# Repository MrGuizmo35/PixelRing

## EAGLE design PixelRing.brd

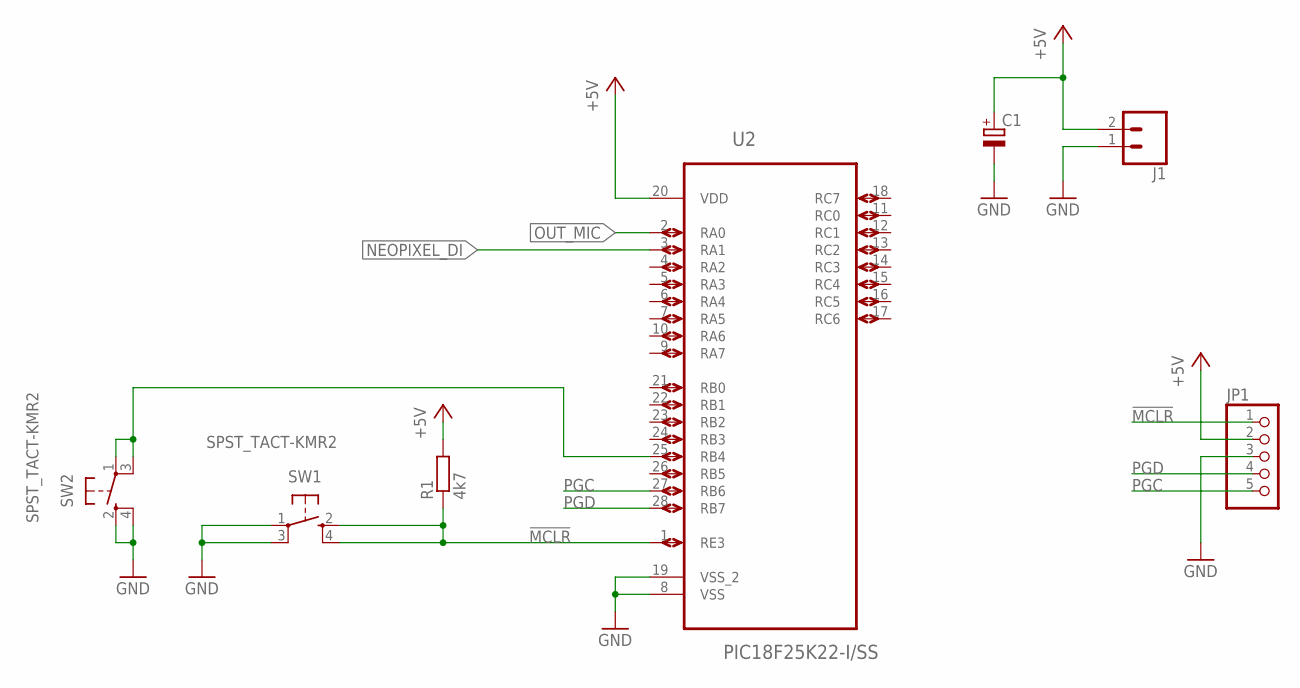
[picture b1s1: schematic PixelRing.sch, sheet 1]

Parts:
C1: CPOL-EUSMCB; SMC_B
J1: CONN_02-JST-2MM-SMT; JST-2-SMD
JP1: PINHD-1X5; 1X05
R1: 4k7; R0603
SW1, SW2: SPST_TACT-KMR2; KMR2
U2: PIC18F25K22-I/SS; SOP65P780X200-28N

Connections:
!MCLR: JP1.1, R1.1, SW1.2 (S), SW1.4 (S1), U2.1 (RE3)
+5V: C1.+, J1.2 (1), JP1.2, R1.2, U2.20 (VDD); also elsewhere on the board
GND: C1.-, J1.1 (2), JP1.3, SW1.1, SW1.3 (P1), SW2.2 (S), SW2.4 (S1), U2.8 (VSS), U2.19 (VSS_2); also elsewhere on the board
unnamed: SW2.1, SW2.3 (P1), U2.25 (RB4)
NEOPIXEL_DI: U2.3 (RA1); also elsewhere on the board
OUT_MIC: U2.2 (RA0); also elsewhere on the board
PGC: JP1.5, U2.27 (RB6)
PGD: JP1.4, U2.28 (RB7)

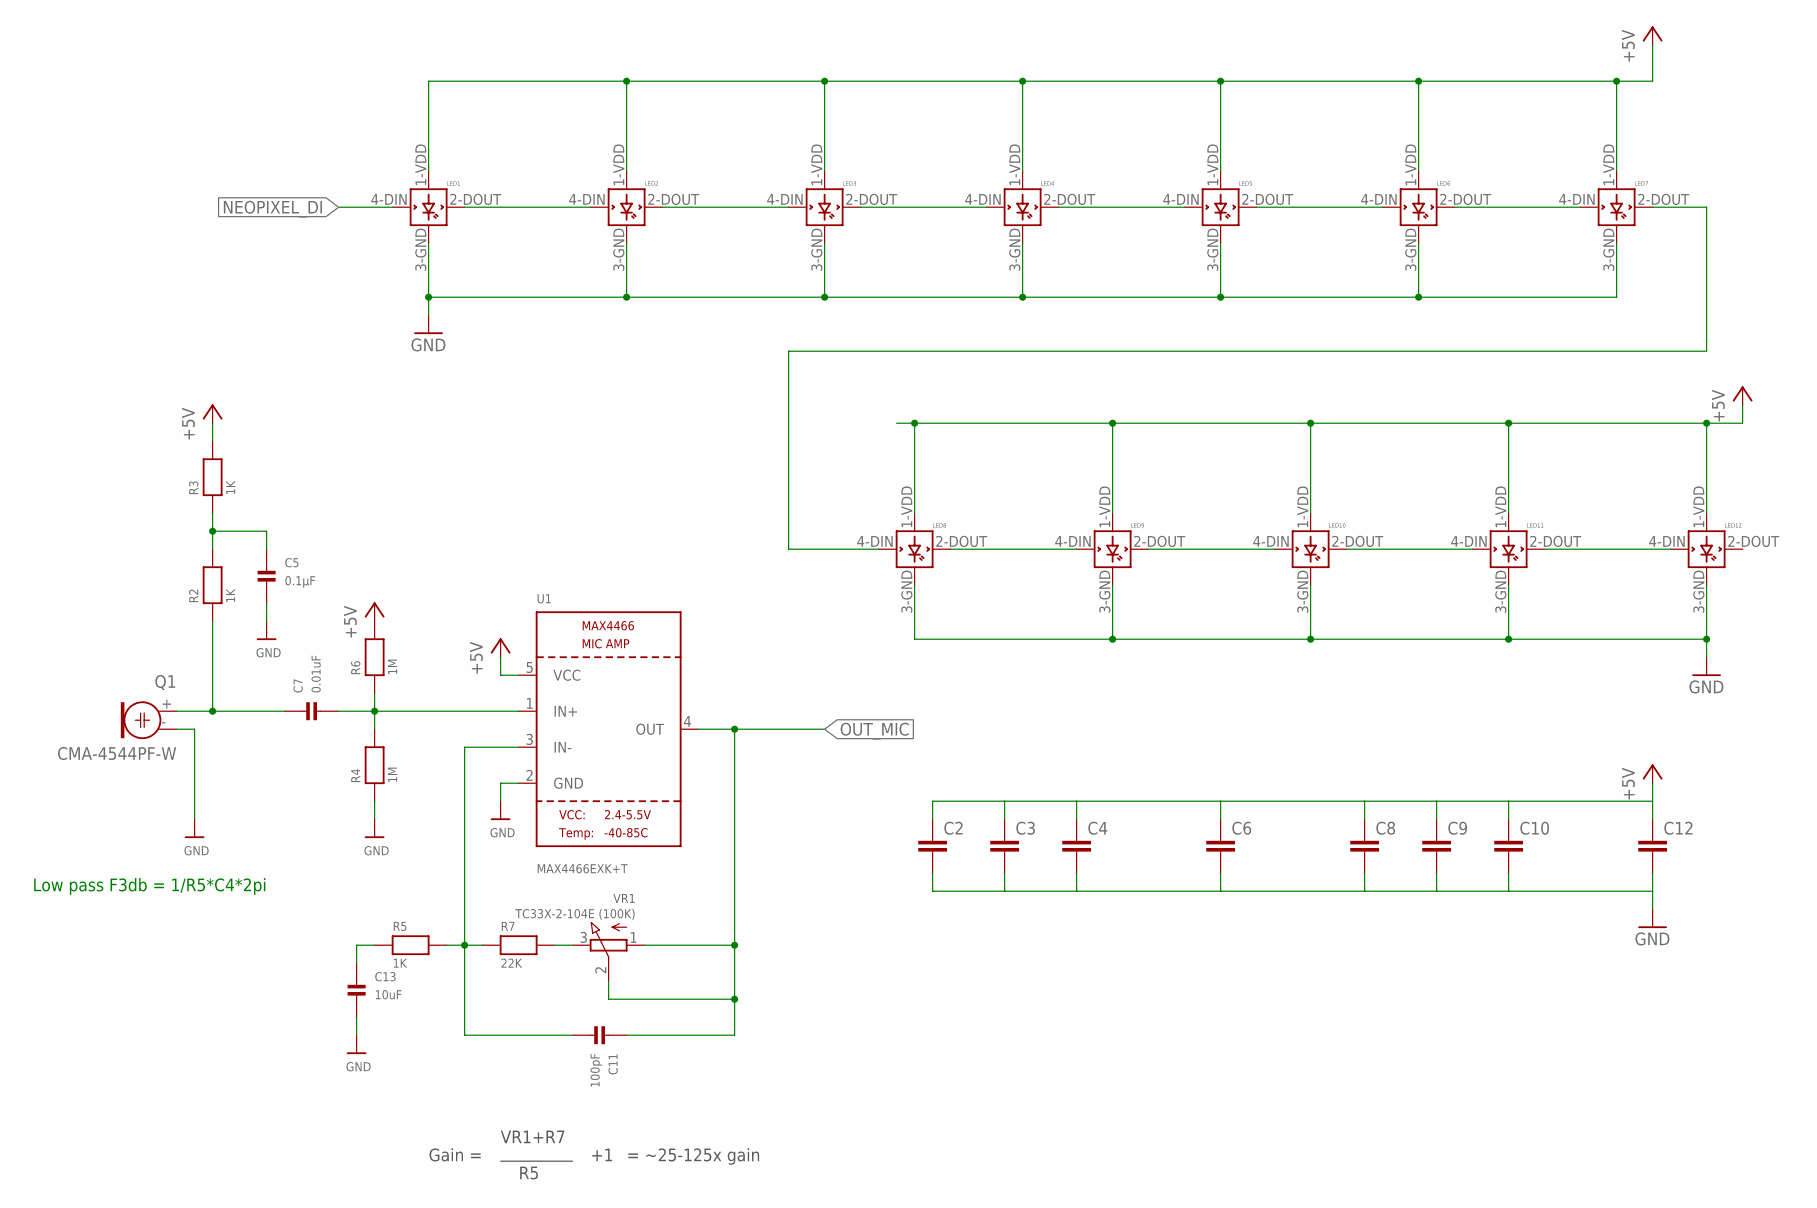
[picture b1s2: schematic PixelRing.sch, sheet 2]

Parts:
C2, C3, C4, C6, C8, C9, C10, C12: C-EUC0603; C0603
C5: 0.1µF; 0805
C7: 0.01uF; 0805
C11: 100pF; 0805
C13: 10uF; 0805
LED1, LED2, LED3, LED4, LED5, LED6, LED7, LED8, LED9, LED10, LED11, LED12: WS2812B
Q1: CMA-4544PF-W; ELECTRET_9.7
R2, R3, R5: 1K; 0805
R4, R6: 1M; 0805
R7: 22K; 0805
U1: MAX4466EXK+T; SC70-5
VR1: TC33X-2-104E (100K); TRIMPOT_BOURNS_TC33X-2

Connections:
+5V: C2.1, C3.1, C4.1, C6.1, C8.1, C9.1, C10.1, C12.1, LED1.1-VDD (VDD), LED2.1-VDD (VDD), LED3.1-VDD (VDD), LED4.1-VDD (VDD), LED5.1-VDD (VDD), LED6.1-VDD (VDD), LED7.1-VDD (VDD), LED8.1-VDD (VDD), LED9.1-VDD (VDD), LED10.1-VDD (VDD), LED11.1-VDD (VDD), LED12.1-VDD (VDD), R3.2, R6.2, U1.5 (VCC); also elsewhere on the board
GND: C2.2, C3.2, C4.2, C5.2, C6.2, C8.2, C9.2, C10.2, C12.2, C13.2, LED1.3-GND (GND), LED2.3-GND (GND), LED3.3-GND (GND), LED4.3-GND (GND), LED5.3-GND (GND), LED6.3-GND (GND), LED7.3-GND (GND), LED8.3-GND (GND), LED9.3-GND (GND), LED10.3-GND (GND), LED11.3-GND (GND), LED12.3-GND (GND), Q1.- (1), R4.1, U1.2 (GND); also elsewhere on the board
unnamed: LED1.2-DOUT (DOUT), LED2.4-DIN (DIN)
unnamed: LED2.2-DOUT (DOUT), LED3.4-DIN (DIN)
unnamed: LED3.2-DOUT (DOUT), LED4.4-DIN (DIN)
unnamed: LED4.2-DOUT (DOUT), LED5.4-DIN (DIN)
unnamed: LED5.2-DOUT (DOUT), LED6.4-DIN (DIN)
unnamed: LED6.2-DOUT (DOUT), LED7.4-DIN (DIN)
unnamed: LED7.2-DOUT (DOUT), LED8.4-DIN (DIN)
unnamed: LED8.2-DOUT (DOUT), LED9.4-DIN (DIN)
unnamed: LED9.2-DOUT (DOUT), LED10.4-DIN (DIN)
unnamed: LED10.2-DOUT (DOUT), LED11.4-DIN (DIN)
unnamed: LED11.2-DOUT (DOUT), LED12.4-DIN (DIN)
unnamed: C7.1, Q1.+ (2), R2.1
unnamed: C5.1, R2.2, R3.1
unnamed: C7.2, R4.2, R6.1, U1.1 (IN+)
unnamed: C11.2, R5.2, R7.1, U1.3 (IN-)
unnamed: C13.1, R5.1
unnamed: R7.2, VR1.3 (E)
NEOPIXEL_DI: LED1.4-DIN (DIN); also elsewhere on the board
OUT_MIC: C11.1, U1.4 (OUT), VR1.1 (A), VR1.2 (S); also elsewhere on the board

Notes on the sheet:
Gain =
VR1+R7
= ~25-125x gain
Low pass F3db = 1/R5*C4*2pi

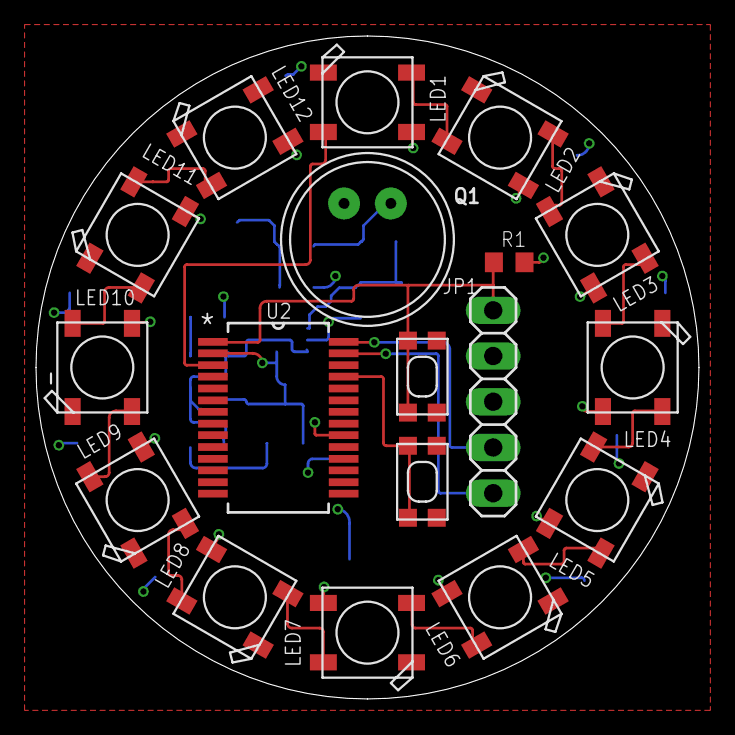
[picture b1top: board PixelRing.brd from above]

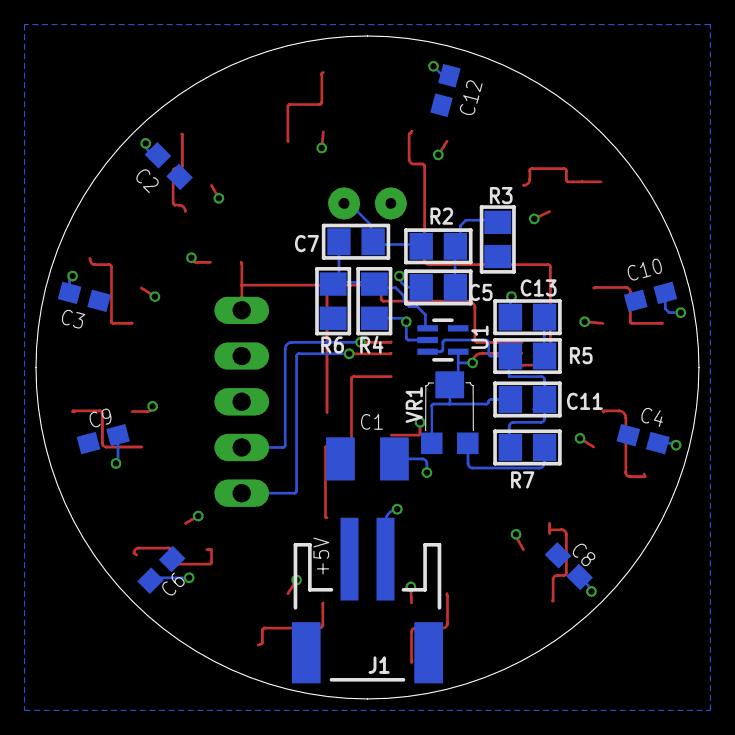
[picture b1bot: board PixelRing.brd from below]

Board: 2 copper layers, 36.8 x 36.8 mm, 40 parts (22 on the bottom side), 25 nets.

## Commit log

2017-10-26 Add files via upload
    Changed micro

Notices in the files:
parts and their libraries:
SparkFun-Connectors: Licensing: Creative Commons ShareAlike 4.0 International - https://creativecommons.org/licenses/by-sa/4.0
microbuilder: This work is placed in the public domain, and may be freely used for commercial and non-commercial work with the following conditions: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
